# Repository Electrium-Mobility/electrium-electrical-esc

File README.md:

# Electrium ESC V1.0

This is Electrium's version of the Electronic Speed Controller (dubbed the BESC). Heavy reference was from the VESC 4.11 model from here: https://github.com/vedderb/bldc-hardware.

## Getting Started

The first thing required is to install KiCad from here: https://www.kicad.org/. Once downloaded, you should be able to pull from the repo and open the project. There are multiple embedded sheets from the top view that you can access.

## Sheets

#### MCU

The MCU is responsible for the control of the entire circuit. This includes getting Firmware uploaded, controlling the Motor, and receiving signals from the remote control. It is the main brain of the ESC!

#### Motor Driver

The Motor Driver takes in a PWM signal and controls the respective Power MOSFETs with those PWM signals. The driver is very important as it is used for low-voltage compatibility, transient protection, and fast switching speed.

#### Power MOSFETs

Power MOSFETs are used to drive the BLDC motor. (Angelina write something :D)

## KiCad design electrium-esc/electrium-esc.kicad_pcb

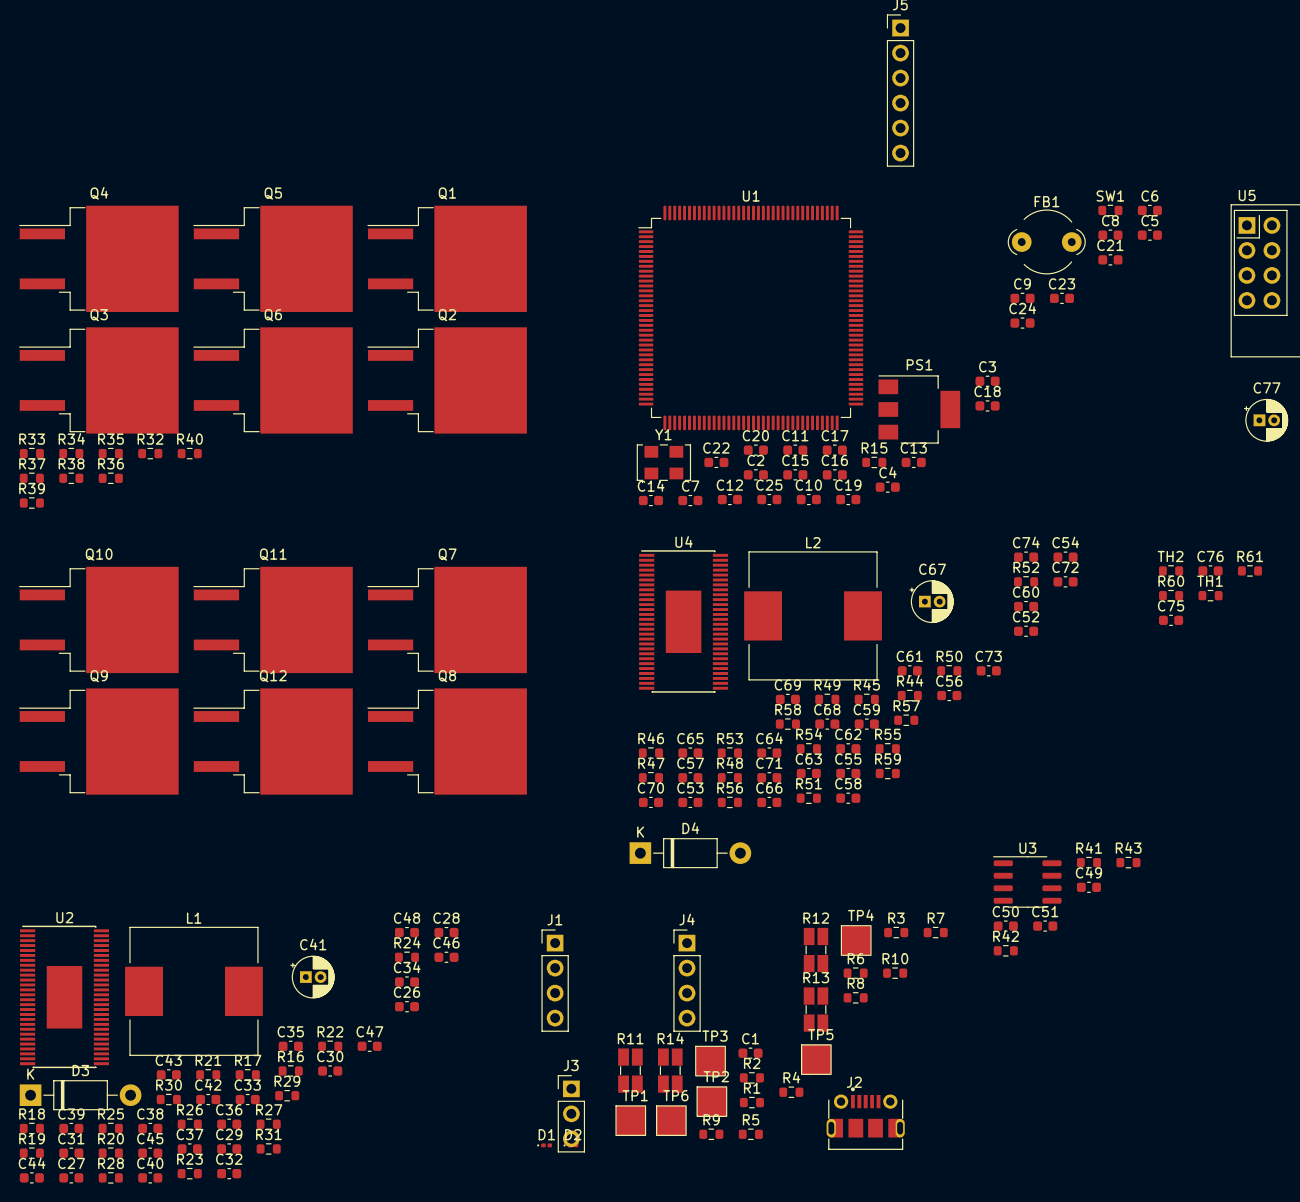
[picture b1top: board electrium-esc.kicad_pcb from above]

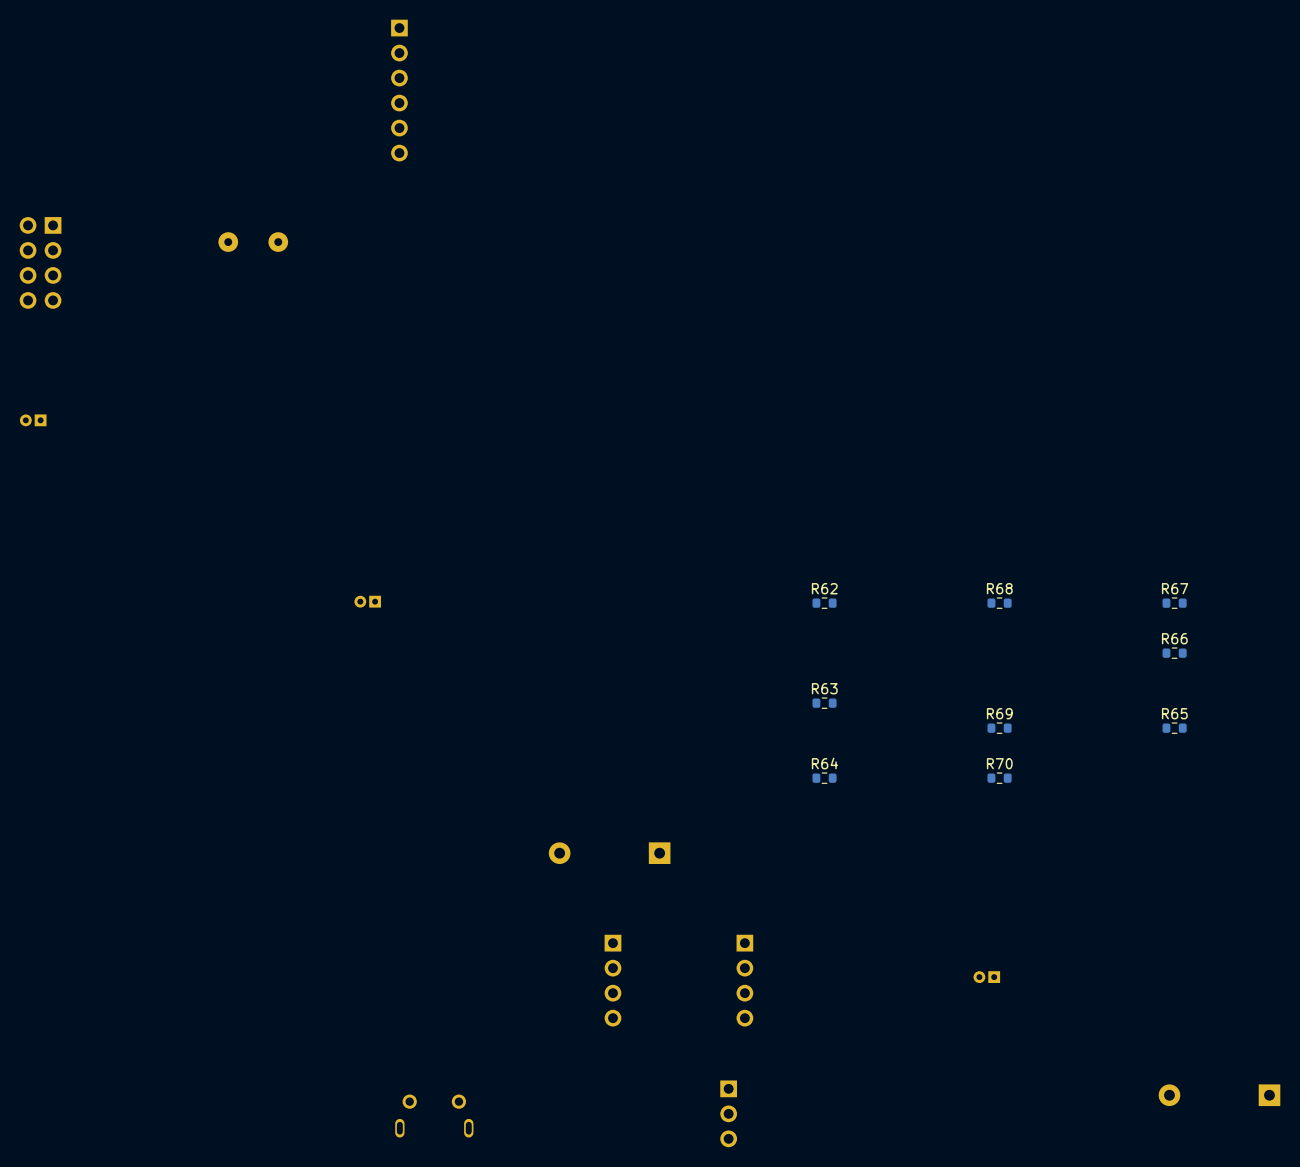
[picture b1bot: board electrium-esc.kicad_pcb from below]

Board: 2 copper layers, 187 parts (9 on the bottom side), 150 nets, no tracks yet.

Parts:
C1, C2, C13, C14, C15, C16, C17, C18, C19, C20, C21, C22, C23, C24, C25, C49, C50, C51: 100n; C_0603_1608Metric
C3, C6, C7, C8, C27, C53, C75, C76: 2.2u; C_0603_1608Metric
C4, C5: 27p; C_0603_1608Metric
C9, C10, C28, C31, C54, C57: 1u; C_0603_1608Metric
C11: 10n; C_0603_1608Metric
C12: 4.7u; C_0603_1608Metric
C26, C52: 120p; C_0603_1608Metric
C29, C55: 6.8n; C_0603_1608Metric
C30, C56: 22n; C_0603_1608Metric
C32, C37, C38, C39, C42, C44, C46, C47, C58, C63, C64, C65, C68, C70, C72, C73: 10u; C_0603_1608Metric
C33, C34, C35, C36, C59, C60, C61, C62: 0.1u; C_0603_1608Metric
C40, C43, C66, C69: 1n; C_0603_1608Metric
C41, C67, C77: 47u; CP_Radial_D4.0mm_P1.50mm
C45, C48, C71, C74: 15u; C_0603_1608Metric
D1, D2: LED; D_0201_0603Metric
D3, D4: 1N5819; D_DO-41_SOD81_P10.16mm_Horizontal
FB1: 120R; LairdTech_28C0236-0JW-10
J1, J4: Conn_01x04_Male; PinHeader_1x04_P2.54mm_Vertical
J2: USB_MICRO; MOLEX_1050170001
J3: Conn_01x03_Male; PinHeader_1x03_P2.54mm_Vertical
J5: Debug Connector; PinHeader_1x06_P2.54mm_Vertical
L1, L2: 22u; L_Wuerth_HCI-1335
PS1: TC2117-3.3VDBTR; SOT-223
Q1, Q2, Q3, Q4, Q5, Q6, Q7, Q8, Q9, Q10, Q11, Q12: IRFS7530TRLPBF; TO-263-2
R1, R2, R7, R29, R30, R31, R57, R58, R59: 2k2; R_0603_1608Metric
R3, R26, R27, R28, R34, R37, R40, R54, R55, R56, R64, R67, R70: 39k; R_0603_1608Metric
R4, R5, R6, R9, R10: 0; R_0603_1608Metric
R8, R22, R23, R24, R25, R50, R51, R52, R53: 100; R_0603_1608Metric
R11, R12, R13, R14: SHUNT; R_Shunt_Ohmite_LVK12
R15, R17, R19, R20, R45, R47, R48, R60, R61: 10k; R_0603_1608Metric
R16, R44: 31k6; R_0603_1608Metric
R18, R46: 15k; R_0603_1608Metric
R21, R49: 220k; R_0603_1608Metric
R32, R33, R35, R36, R38, R39, R62, R63, R65, R66, R68, R69: 4R7; R_0603_1608Metric
R41, R42: 10; R_0603_1608Metric
R43: IN; R_0603_1608Metric
SW1: SW_SPDT; R_0603_1608Metric
TH1, TH2: Thermistor_PTC; R_0603_1608Metric
TP1: M_1A; MOTOR_PAD
TP2: M_2A; MOTOR_PAD
TP3: M_3A; MOTOR_PAD
TP4: M_1B; MOTOR_PAD
TP5: M_2B; MOTOR_PAD
TP6: M_3B; MOTOR_PAD
U1: STM32F407ZGT6; LQFP-144_20x20mm_P0.5mm
U2, U4: DRV8301DCAR; HTSSOP-56-1EP_6.1x14mm_P0.5mm_EP3.61x6.35mm
U3: SN65HVD232; SOIC-8_3.9x4.9mm_P1.27mm
U5: NRF24L01_Breakout; nRF24L01_Breakout
Y1: 25MHz; Oscillator_SMD_TXC_7C-4Pin_5.0x3.2mm

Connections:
+3.3V: C7.1, C9.1, C12.1, C13.1, C14.1, C15.1, C16.1, C17.1, C18.1, C19.1, C20.1, C21.1, C22.1, C23.1, C24.1, C25.1, C41.1, C49.1, C50.1, C51.1, C67.1, C77.1, FB1.1, J4.1, J5.6, L1.2, L2.2, PS1.4 (VOUT_2), R1.2, R16.1, R19.1, R44.1, R47.1, TH1.1, TH2.1, U1.6 (VBAT), U1.17 (VDD), U1.30 (VDD), U1.32 (VREF+), U1.39 (VDD), U1.52 (VDD), U1.62 (VDD), U1.72 (VDD), U1.84 (VDD), U1.89 (PG4), U1.92 (PG7), U1.95 (VDD), U1.108 (VDD), U1.121 (VDD), U1.131 (VDD), U1.143 (PDR_ON), U1.144 (VDD), U2.24 (REF), U2.49 (VDD_SPI), U3.3 (VCC), U4.24 (REF), U4.49 (VDD_SPI), U5.2 (VCC)
+3.3VA: C10.1, C11.1, FB1.2, U1.33 (VDDA)
+5V: C3.2, J1.1, J3.2, PS1.3 (VIN), R4.1
/AN_IN: R2.2, R3.1, U1.14 (PF4)
/CANH: J1.2, R43.1, U3.7 (CANH)
/CANL: J1.3, R43.2, U3.6 (CANL)
/CAN_RX: R42.2, U1.114 (PD0)
/CAN_TX: R41.1, U1.115 (PD1)
/MCU (STM32F407ZGT6)/BOOT0: R15.2, U1.138 (BOOT0)
/MCU (STM32F407ZGT6)/BR_SO1_A: U1.20 (PF8_(ADC)), U2.25 (SO1)
/MCU (STM32F407ZGT6)/BR_SO1_B: U1.28 (PC2_(ADC)), U4.25 (SO1)
/MCU (STM32F407ZGT6)/BR_SO2_A: U1.21 (PF9_(ADC)), U2.26 (SO2)
/MCU (STM32F407ZGT6)/BR_SO2_B: U1.29 (PC3_(ADC)), U4.26 (SO2)
/MCU (STM32F407ZGT6)/CS_A: U1.110 (PA15), U2.8 (N_SCS)
/MCU (STM32F407ZGT6)/CS_B: U1.74 (PB13), U4.8 (N_SCS)
/MCU (STM32F407ZGT6)/DC_CAL_A: U1.91 (PG6), U2.12 (DC_CAL)
/MCU (STM32F407ZGT6)/DC_CAL_B: U1.88 (PG3), U4.12 (DC_CAL)
/MCU (STM32F407ZGT6)/EN_GATE_A: U1.90 (PG5), U2.16 (EN_GATE)
/MCU (STM32F407ZGT6)/EN_GATE_B: U1.87 (PG2), U4.16 (EN_GATE)
/MCU (STM32F407ZGT6)/GPIO1: R9.2, U1.34 (PA0)
/MCU (STM32F407ZGT6)/GPIO2: R10.2, U1.35 (PA1)
/MCU (STM32F407ZGT6)/H1_A: U1.97 (PC7), U2.17 (INH_A)
/MCU (STM32F407ZGT6)/H1_B: U1.67 (PE14), U4.17 (INH_A)
/MCU (STM32F407ZGT6)/H2_A: U1.86 (PD15), U2.19 (INH_B)
/MCU (STM32F407ZGT6)/H2_B: U1.64 (PE11), U4.19 (INH_B)
/MCU (STM32F407ZGT6)/H3_A: U1.82 (PD13), U2.21 (INH_C)
/MCU (STM32F407ZGT6)/H3_B: U1.47 (PB1), U4.22 (INL_C)
/MCU (STM32F407ZGT6)/HSE_IN: C4.1, U1.23 (PH0), Y1.1
/MCU (STM32F407ZGT6)/HSE_OUT: C5.1, U1.24 (PH1), Y1.3
/MCU (STM32F407ZGT6)/L1_A: U1.96 (PC6), U2.18 (INL_A)
/MCU (STM32F407ZGT6)/L1_B: U1.66 (PE13), U4.18 (INL_A)
/MCU (STM32F407ZGT6)/L2_A: U1.85 (PD14), U2.20 (INL_B)
/MCU (STM32F407ZGT6)/L2_B: U1.60 (PE9), U4.20 (INL_B)
/MCU (STM32F407ZGT6)/L3_A: U1.81 (PD12), U2.22 (INL_C)
/MCU (STM32F407ZGT6)/L3_B: U1.46 (PB0), U4.21 (INH_C)
/MCU (STM32F407ZGT6)/LED: R8.2, U1.137 (PB7)
/MCU (STM32F407ZGT6)/MISO_A: U1.112 (PC11_(MISO)), U2.10 (SDO)
/MCU (STM32F407ZGT6)/MISO_B: U1.75 (PB14_(MISO)), U4.10 (SDO)
/MCU (STM32F407ZGT6)/MOSI_A: U1.113 (PC12_(MOSI)), U2.9 (SDI)
/MCU (STM32F407ZGT6)/MOSI_B: U1.76 (PB15_(MOSI)), U4.9 (SDI)
/MCU (STM32F407ZGT6)/NRF_CE: U1.40 (PA4), U5.3 (CE)
/MCU (STM32F407ZGT6)/NRF_CSN: U1.37 (PA3), U5.4 (~CSN)
/MCU (STM32F407ZGT6)/NRF_MISO: U1.42 (PA6_(MISO)), U5.7 (MISO)
/MCU (STM32F407ZGT6)/NRF_MOSI: U1.43 (PA7_(MOSI)), U5.6 (MOSI)
/MCU (STM32F407ZGT6)/NRF_SCK: U1.41 (PA5_(SCK)), U5.5 (SCK)
/MCU (STM32F407ZGT6)/SCK_A: U1.111 (PC10_(SCK)), U2.11 (SCLK)
/MCU (STM32F407ZGT6)/SCK_B: U1.69 (PB10_(SCK)), U4.11 (SCLK)
/MCU (STM32F407ZGT6)/SENS1_A: R26.1, R29.2, U1.15 (PF5_(ADC))
/MCU (STM32F407ZGT6)/SENS1_B: R54.1, R57.2, U1.22 (PF10_(ADC))
/MCU (STM32F407ZGT6)/SENS2_A: R27.1, R30.2, U1.18 (PF6_(ADC))
/MCU (STM32F407ZGT6)/SENS2_B: R55.1, R58.2, U1.26 (PC0_(ADC))
/MCU (STM32F407ZGT6)/SENS3_A: R28.1, R31.2, U1.19 (PF7_(ADC))
/MCU (STM32F407ZGT6)/SENS3_B: R56.1, R59.2, U1.27 (PC1_(ADC))
/MCU (STM32F407ZGT6)/SERVO: C1.1, R7.1, U1.36 (PA2)
/MCU (STM32F407ZGT6)/SWO: J5.1, U1.133 (PB3)
/MCU (STM32F407ZGT6)/SW_BOOT0: R15.1, SW1.2 (B)
/MCU (STM32F407ZGT6)/TEMP_A: C75.1, R60.1, TH1.2, U1.44 (PC4_(ADC))
/MCU (STM32F407ZGT6)/TEMP_B: C76.1, R61.1, TH2.2, U1.45 (PC5_(ADC))
/MCU (STM32F407ZGT6)/USB_D+: R6.1, U1.104 (PA12)
/MCU (STM32F407ZGT6)/USB_D-: R5.1, U1.103 (PA11)
/Motor Driver A (DRV8301)/AVDD: C31.1, U2.27 (AVDD)
/Motor Driver A (DRV8301)/COMP: C26.2, R18.1, U2.2 (COMP)
/Motor Driver A (DRV8301)/DTC: R20.2, U2.7 (DTC)
/Motor Driver A (DRV8301)/DVDD: C28.2, U2.23 (DVDD)
/Motor Driver A (DRV8301)/GVDD: C27.2, U2.13 (GVDD)
/Motor Driver A (DRV8301)/H1_LOW: Q2.3 (S), R13.1, R24.1, R34.2, R37.1, U2.44 (SL_A)
/Motor Driver A (DRV8301)/H1_VS: C34.2, Q1.3 (S), Q2.2 (D), R26.2, TP1.1, U2.46 (SH_A)
/Motor Driver A (DRV8301)/H2_VS: C35.2, Q3.3 (S), Q4.2 (D), R27.2, TP2.1, U2.41 (SH_B)
/Motor Driver A (DRV8301)/H3_LOW: Q6.3 (S), R11.1, R22.1, R40.2, U2.34 (SL_C)
/Motor Driver A (DRV8301)/H3_VS: C36.2, Q5.3 (S), Q6.2 (D), R28.2, TP3.1, U2.36 (SH_C)
/Motor Driver A (DRV8301)/M_H1: R32.1, U2.47 (GH_A)
/Motor Driver A (DRV8301)/M_H2: R35.2, U2.42 (GH_B)
/Motor Driver A (DRV8301)/M_H3: R38.2, U2.37 (GH_C)
/Motor Driver A (DRV8301)/M_L1: R33.1, U2.45 (GL_A)
/Motor Driver A (DRV8301)/M_L2: R36.2, U2.40 (GL_B)
/Motor Driver A (DRV8301)/M_L3: R39.2, U2.35 (GL_C)
/Motor Driver A (DRV8301)/NFAULT: R19.2, U2.6 (N_FAULT)
/Motor Driver A (DRV8301)/VSENSE: R16.2, R17.1, U2.3 (VSENSE)
/Motor Driver B (DRV8301)/AVDD: C57.1, U4.27 (AVDD)
/Motor Driver B (DRV8301)/COMP: C52.2, R46.1, U4.2 (COMP)
/Motor Driver B (DRV8301)/DTC: R48.2, U4.7 (DTC)
/Motor Driver B (DRV8301)/DVDD: C54.2, U4.23 (DVDD)
/Motor Driver B (DRV8301)/GVDD: C53.2, U4.13 (GVDD)
/Motor Driver B (DRV8301)/H1_LOW: Q8.3 (S), R14.1, R52.1, R64.2, R67.1, U4.44 (SL_A)
/Motor Driver B (DRV8301)/H1_VS: C60.2, Q7.3 (S), Q8.2 (D), R54.2, TP4.1, U4.46 (SH_A)
/Motor Driver B (DRV8301)/H2_VS: C61.2, Q9.3 (S), Q10.2 (D), R55.2, TP5.1, U4.41 (SH_B)
/Motor Driver B (DRV8301)/H3_LOW: Q12.3 (S), R12.1, R50.1, R70.2, U4.34 (SL_C)
/Motor Driver B (DRV8301)/H3_VS: C62.2, Q11.3 (S), Q12.2 (D), R56.2, TP6.1, U4.36 (SH_C)
/Motor Driver B (DRV8301)/M_H1: R62.1, U4.47 (GH_A)
/Motor Driver B (DRV8301)/M_H2: R65.2, U4.42 (GH_B)
/Motor Driver B (DRV8301)/M_H3: R68.2, U4.37 (GH_C)
/Motor Driver B (DRV8301)/M_L1: R63.1, U4.45 (GL_A)
/Motor Driver B (DRV8301)/M_L2: R66.2, U4.40 (GL_B)
/Motor Driver B (DRV8301)/M_L3: R69.2, U4.35 (GL_C)
/Motor Driver B (DRV8301)/NFAULT: R47.2, U4.6 (N_FAULT)
/Motor Driver B (DRV8301)/VSENSE: R44.2, R45.1, U4.3 (VSENSE)
GND: C1.2, C2.2, C3.1, C4.2, C5.2, C6.2, C7.2, C8.2, C9.2, C10.2, C11.2, C12.2, C13.2, C14.2, C15.2, C16.2, C17.2, C18.2, C19.2, C20.2, C21.2, C22.2, C23.2, C24.2, C25.2, C26.1, C27.1, C28.1, C29.1, C31.2, C32.2, C37.1, C38.2, C39.2, C41.2, C42.2, C44.2, C45.2, C46.2, C47.2, C48.2, C50.2, C51.2, C52.1, C53.1, C54.1, C55.1, C57.2, C58.2, C63.1, C64.2, C65.2, C67.2, C68.2, C70.2, C71.2, C72.2, C73.2, C74.2, C75.2, C76.2, C77.2, D1.1 (K), D2.1 (K), D3.2 (A), D4.2 (A), J1.4, J2.5, J3.3, J4.4, J5.4, PS1.1 (GND), Q4.3 (S), Q10.3 (S), R2.1, R11.2, R12.2, R13.2, R14.2, R17.2, R20.1, R21.1, R23.1, R25.1, R29.1, R30.1, R31.1, R45.2, R48.1, R49.1, R51.1, R53.1, R57.1, R58.1, R59.1, R60.2, R61.2, SW1.1 (A), U1.16 (VSS), U1.31 (VSSA), U1.38 (VSS), U1.51 (VSS), U1.61 (VSS), U1.83 (VSS), U1.94 (VSS), U1.107 (VSS), U1.120 (VSS), U1.130 (VSS), U2.28 (AGND), U2.39 (SL_B), U2.57 (EP), U3.2 (GND), U4.28 (AGND), U4.39 (SL_B), U4.57 (EP), U5.1 (GND), Y1.2, Y1.4
NRST: C2.1, J5.2, U1.25 (NRST)
unnamed: C6.1, C8.1, U1.71 (VCAP_1), U1.106 (VCAP_2)
unnamed: C29.2, R18.2
unnamed: C30.1, U2.15 (CP2)
unnamed: C30.2, U2.14 (CP1)
unnamed: C33.1, U2.52 (BST_BK)
unnamed: C33.2, D3.1 (K), L1.1, U2.50 (PH_1), U2.51 (PH_2)
unnamed: C34.1, U2.48 (BST_A)
unnamed: C35.1, U2.43 (BST_B)
unnamed: C36.1, U2.38 (BST_C)
unnamed: C40.1, R22.2, U2.33 (SN1)
unnamed: C40.2, R23.2, U2.32 (SP1)
unnamed: C43.1, R24.2, U2.31 (SN2)
unnamed: C43.2, R25.2, U2.30 (SP2)
unnamed: C49.2, R41.2, U3.1 (D)
unnamed: C55.2, R46.2
unnamed: C56.1, U4.15 (CP2)
unnamed: C56.2, U4.14 (CP1)
unnamed: C59.1, U4.52 (BST_BK)
unnamed: C59.2, D4.1 (K), L2.1, U4.50 (PH_1), U4.51 (PH_2)
unnamed: C60.1, U4.48 (BST_A)
unnamed: C61.1, U4.43 (BST_B)
unnamed: C62.1, U4.38 (BST_C)
unnamed: C66.1, R50.2, U4.33 (SN1)
unnamed: C66.2, R51.2, U4.32 (SP1)
unnamed: C69.1, R52.2, U4.31 (SN2)
unnamed: C69.2, R53.2, U4.30 (SP2)
unnamed: D1.2 (A), R1.1
unnamed: D2.2 (A), R8.1
unnamed: J2.1, R4.2
unnamed: J2.2, R5.2
unnamed: J2.3, R6.2
unnamed: J3.1, R7.2
unnamed: J4.2, R10.1
unnamed: J4.3, R9.1
unnamed: Q1.1 (G), R32.2
unnamed: Q2.1 (G), R33.2, R34.1
unnamed: Q3.1 (G), R35.1
unnamed: Q4.1 (G), R36.1, R37.2
unnamed: Q5.1 (G), R38.1
unnamed: Q6.1 (G), R39.1, R40.1
unnamed: Q7.1 (G), R62.2
unnamed: Q8.1 (G), R63.2, R64.1
unnamed: Q9.1 (G), R65.1
unnamed: Q10.1 (G), R66.1, R67.2
unnamed: Q11.1 (G), R68.1
unnamed: Q12.1 (G), R69.1, R70.1
unnamed: R21.2, U2.1 (RT_CLK)
unnamed: R42.1, U3.4 (R)
unnamed: R49.2, U4.1 (RT_CLK)
SWCLK: J5.5, U1.109 (PA14)
SWDIO: J5.3, U1.105 (PA13)
V_SUPPLY: C32.1, C37.2, C38.1, C39.1, C42.1, C44.1, C45.1, C46.1, C47.1, C48.1, C58.1, C63.2, C64.1, C65.1, C68.1, C70.1, C71.1, C72.1, C73.1, C74.1, Q1.2 (D), Q3.2 (D), Q5.2 (D), Q7.2 (D), Q9.2 (D), Q11.2 (D), R3.2, U2.29 (PVDD1), U2.53 (PVDD2_1), U2.54 (PVDD2_2), U4.29 (PVDD1), U4.53 (PVDD2_1), U4.54 (PVDD2_2)

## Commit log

2023-01-16 Add top level view
2023-01-17 Add further connections to MCU
2023-01-18 Complete Motor Driver!
    Put in place passive components per documentation
2023-01-19 Add additional MCU connectivity
    Still need to integrate NRF24L01 capabilities
2023-01-20 Add additional connections to MCU
2023-01-21 Connect Temperature Sensors
2023-01-21 Modify title
2023-01-22 Add files via upload
    updating the Power Mosfet's schematics
2023-01-22 Add files via upload
    MCU->Driver
2023-01-22 Delete MOSFETs.kicad_sch
    removed placeholder document
2023-01-22 Rename MOSFETs.kicad_sch to electrium-esc/MOSFETs.kicad_sch
    moved to correct folder
2023-01-22 Update MOSFETs.kicad_sch
    updated schematic with resistor values
2023-01-22 Prototype (almost) finished
    Have to do electric check rules
2023-01-22 Fix Error
2023-01-22 Update Footprints for schematic symbols
2023-01-22 Create motor pad footprint
2023-01-22 Update footprints
2023-01-23 Initial placement prototype
2023-01-25 relabel components to make more sense
2023-01-25 Add power caps
2023-01-25 add all additional design changes (good to go)
    Note: may need to change some footprints depending on what's available
2023-01-25 final version (good to go!)
2023-01-25 Update diodes (real version now)
2023-01-25 initial pcb placement
2023-01-25 Change to cheaper mosfets
2023-01-25 Finished basic layout
2023-01-26 Semi-finished schematic
2023-01-27 Update more components and few traces
    Final design hopefully done by tomorrow. Logistical problems are coming through, needs to suit components to those needs
2023-01-28 Add power connections
    I realize Vias are unrealistic, need to redo.
2023-01-28 Fix most ERC errors, just some connections now!
2023-01-28 Did a bit more work, almost done!
2023-01-28 Add Shunt resistors and fixed DRC errors
2023-01-28 Fix warnings
2023-01-28 Add final touches to board!
2023-01-28 Add Gerber and final files
2023-01-30 finsihed 1 set of power mosfets
    finsihed one set of power mosfets with resistors
